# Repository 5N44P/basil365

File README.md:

# Basil365 (*ARCHIVED - ON HOLD*)
I want fresh basil all year round, but outdoors here it doesn't grow. Let's fix this, and make it IoT.

Buying a growlamp on the internet would be quite easy and cheap, but wouldn't make for a great DIY IoT project, so who cares, i'm going to roll my own IoT growlamp. And i want it to be the best and most efficient growlamp ever made. Since we are there, why not adding a load of sensors and connect it to a telegram bot to harass you? Seems great, let's do it.  

Led board without drivers

Test board (arduino shield) to assess the performance of various drivers and components 

## Initial research

Starting from the lamp, we want it led based. If you've ever seen a led growlamp before, you know that they are made of blue and red LEDs. But maybe we can do better. 

reference:  
https://www.growing-basil.org/artificial-lighting-for-growing-basil/ (secondary source)   
https://www.ncbi.nlm.nih.gov/pmc/articles/PMC5007804/  blue (450 nm), yellow/amber (600 nm), red (660 nm); 1:1:1; 150 μmol m−2 s−1    
https://www.sciencedirect.com/science/article/pii/S0304423815302892    
http://www.hortorumcultus.actapol.net/pub/13_2_3.pdf  

Design and fabrication of adjustable red-green-blue LED light arrays for plant research
https://www.ncbi.nlm.nih.gov/pmc/articles/PMC1198233/

umol/m2s to W/m2 equivalency
https://onlineconversion.vbulletin.net/forum/main-forums/convert-and-calculate/82240-%C2%B5mol-photons-m-2-s-1-to-led-watts

https://www.valoya.com/

Potential led:
Osram oslon ssl80

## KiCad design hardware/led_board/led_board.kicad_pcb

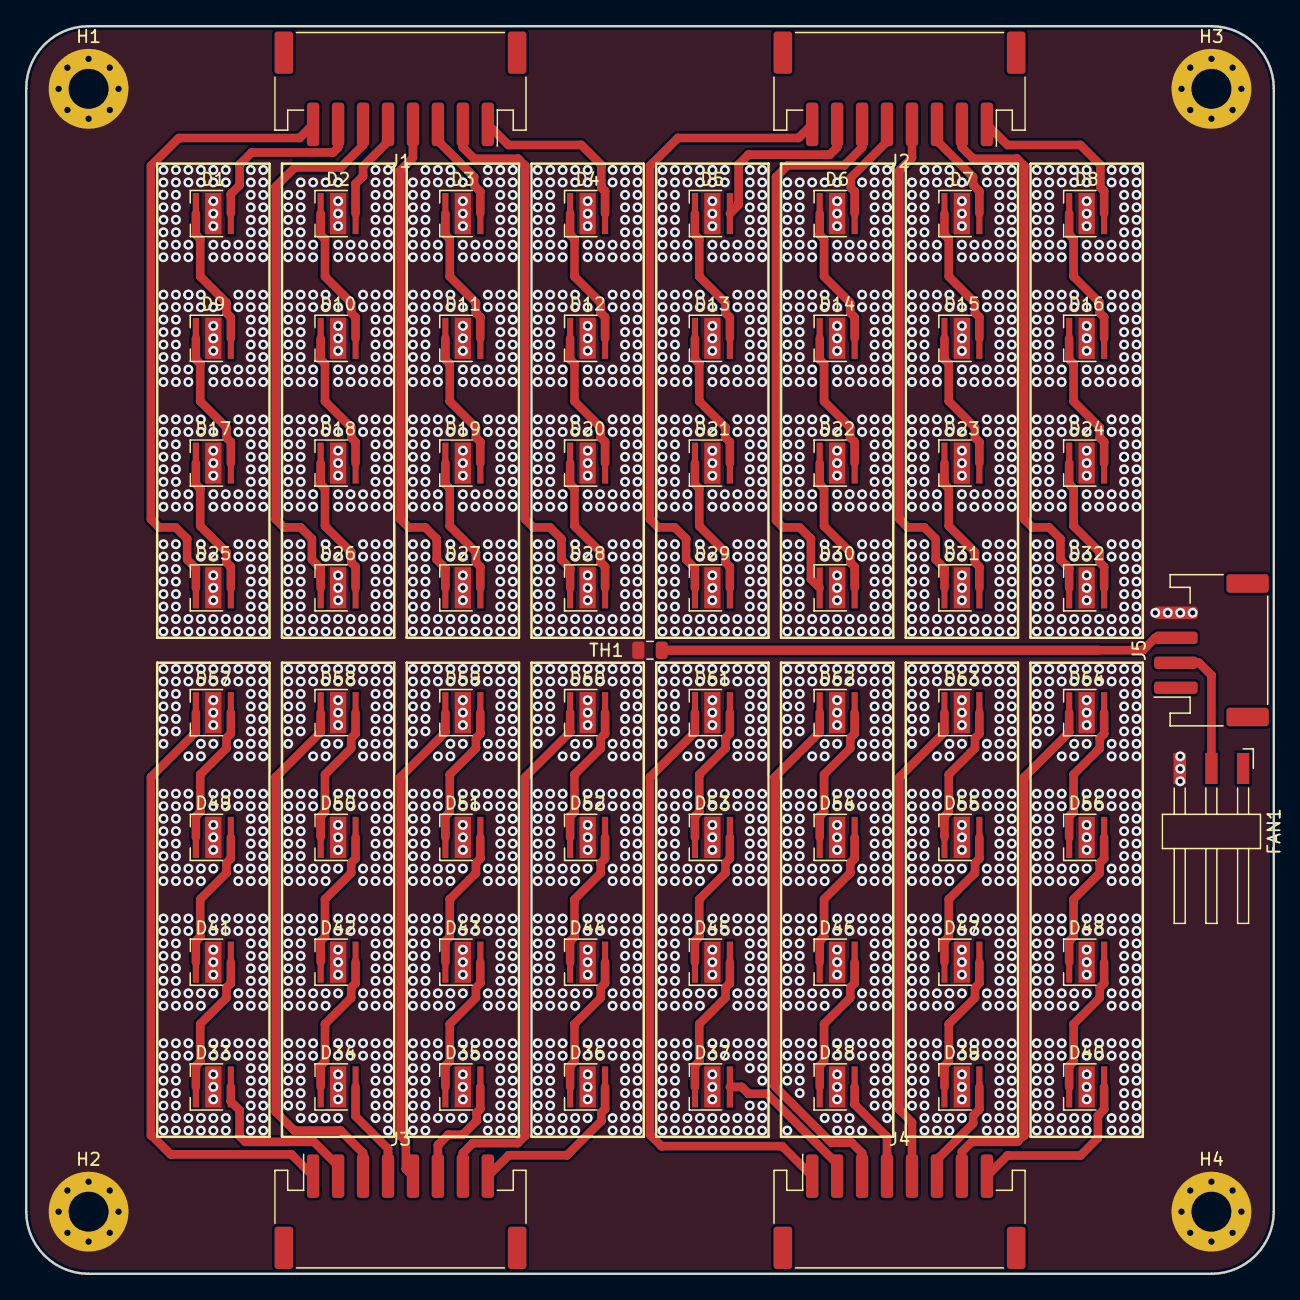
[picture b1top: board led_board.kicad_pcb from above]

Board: 2 copper layers, 100.0 x 100.0 mm, 75 parts (0 on the bottom side), 83 nets.

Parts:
D1, D2, D3, D4, D5, D6, D7, D8, D9, D10, D11, D12, D13, D14, D15, D16, D17, D18, D19, D20, D21, D22, D23, D24, D25, D26, D27, D28, D29, D30, D31, D32, D33, D34, D35, D36, D37, D38, D39, D40, D41, D42, D43, D44, D45, D46, D47, D48, D49, D50, D51, D52, D53, D54, D55, D56, D57, D58, D59, D60, D61, D62, D63, D64: LED_PAD; LED_Cree-XHP35
FAN1: Conn_01x03; Harwin_M20-89003xx_1x03_P2.54mm_Horizontal
H1, H2, H3, H4: MountingHole_Pad; MountingHole_3.2mm_M3_Pad_Via
J1, J2, J3, J4: NXW-08SMDK; JST_PH_S8B-PH-SM4-TB_1x08-1MP_P2.00mm_Horizontal
J5: Conn_01x04; JST_PH_S4B-PH-SM4-TB_1x04-1MP_P2.00mm_Horizontal
TH1: Thermistor_NTC; R_0805_2012Metric

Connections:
DRV1_A: D1.2, J1.7
DRV1_K: D25.1, J1.8
DRV2_A: D2.2, J1.5
DRV2_K: D26.1, J1.6
DRV3_A: D3.2, J1.3
DRV3_K: D27.1, J1.4
DRV4_A: D4.2, J1.1
DRV4_K: D28.1, J1.2
DRV5_A: D5.2, J2.7
DRV5_K: D29.1, J2.8
DRV6_A: D6.2, J2.5
DRV6_K: D30.1, J2.6
DRV7_A: D7.2, J2.3
DRV7_K: D31.1, J2.4
DRV8_A: D8.2, J2.1
DRV8_K: D32.1, J2.2
DRV9_A: D33.2, J3.2
DRV9_K: D57.1, J3.1
DRV10_A: D34.2, J3.4
DRV10_K: D58.1, J3.3
DRV11_A: D35.2, J3.6
DRV11_K: D59.1, J3.5
DRV12_A: D36.2, J3.8
DRV12_K: D60.1, J3.7
DRV13_A: D37.2, J4.2
DRV13_K: D61.1, J4.1
DRV14_A: D38.2, J4.4
DRV14_K: D62.1, J4.3
DRV15_A: D39.2, J4.6
DRV15_K: D63.1, J4.5
DRV16_A: D40.2, J4.8
DRV16_K: D64.1, J4.7
FAN_PWM: FAN1.2, J5.2
GND: D1.3, D2.3, D3.3, D4.3, D5.3, D6.3, D7.3, D8.3, D9.3, D10.3, D11.3, D12.3, D13.3, D14.3, D15.3, D16.3, D17.3, D18.3, D19.3, D20.3, D21.3, D22.3, D23.3, D24.3, D25.3, D26.3, D27.3, D28.3, D29.3, D30.3, D31.3, D32.3, D33.3, D34.3, D35.3, D36.3, D37.3, D38.3, D39.3, D40.3, D41.3, D42.3, D43.3, D44.3, D45.3, D46.3, D47.3, D48.3, D49.3, D50.3, D51.3, D52.3, D53.3, D54.3, D55.3, D56.3, D57.3, D58.3, D59.3, D60.3, D61.3, D62.3, D63.3, D64.3, FAN1.3, H1.1, H2.1, H3.1, H4.1, J5.4, TH1.1
unnamed: D1.1, D9.2
unnamed: D10.1, D18.2
unnamed: D2.1, D10.2
unnamed: D11.1, D19.2
unnamed: D3.1, D11.2
unnamed: D12.1, D20.2
unnamed: D4.1, D12.2
unnamed: D13.1, D21.2
unnamed: D5.1, D13.2
unnamed: D14.1, D22.2
unnamed: D6.1, D14.2
unnamed: D15.1, D23.2
unnamed: D7.1, D15.2
unnamed: D16.1, D24.2
unnamed: D8.1, D16.2
unnamed: D17.1, D25.2
unnamed: D9.1, D17.2
unnamed: D18.1, D26.2
unnamed: D19.1, D27.2
unnamed: D20.1, D28.2
unnamed: D21.1, D29.2
unnamed: D22.1, D30.2
unnamed: D23.1, D31.2
unnamed: D24.1, D32.2
unnamed: D33.1, D41.2
unnamed: D34.1, D42.2
unnamed: D35.1, D43.2
unnamed: D36.1, D44.2
unnamed: D37.1, D45.2
unnamed: D38.1, D46.2
unnamed: D39.1, D47.2
unnamed: D40.1, D48.2
unnamed: D41.1, D49.2
unnamed: D42.1, D50.2
unnamed: D43.1, D51.2
unnamed: D44.1, D52.2
unnamed: D45.1, D53.2
unnamed: D46.1, D54.2
unnamed: D47.1, D55.2
unnamed: D48.1, D56.2
unnamed: D49.1, D57.2
unnamed: D50.1, D58.2
unnamed: D51.1, D59.2
unnamed: D52.1, D60.2
unnamed: D53.1, D61.2
unnamed: D54.1, D62.2
unnamed: D55.1, D63.2
unnamed: D56.1, D64.2
TEMP_SENSE: J5.3, TH1.2

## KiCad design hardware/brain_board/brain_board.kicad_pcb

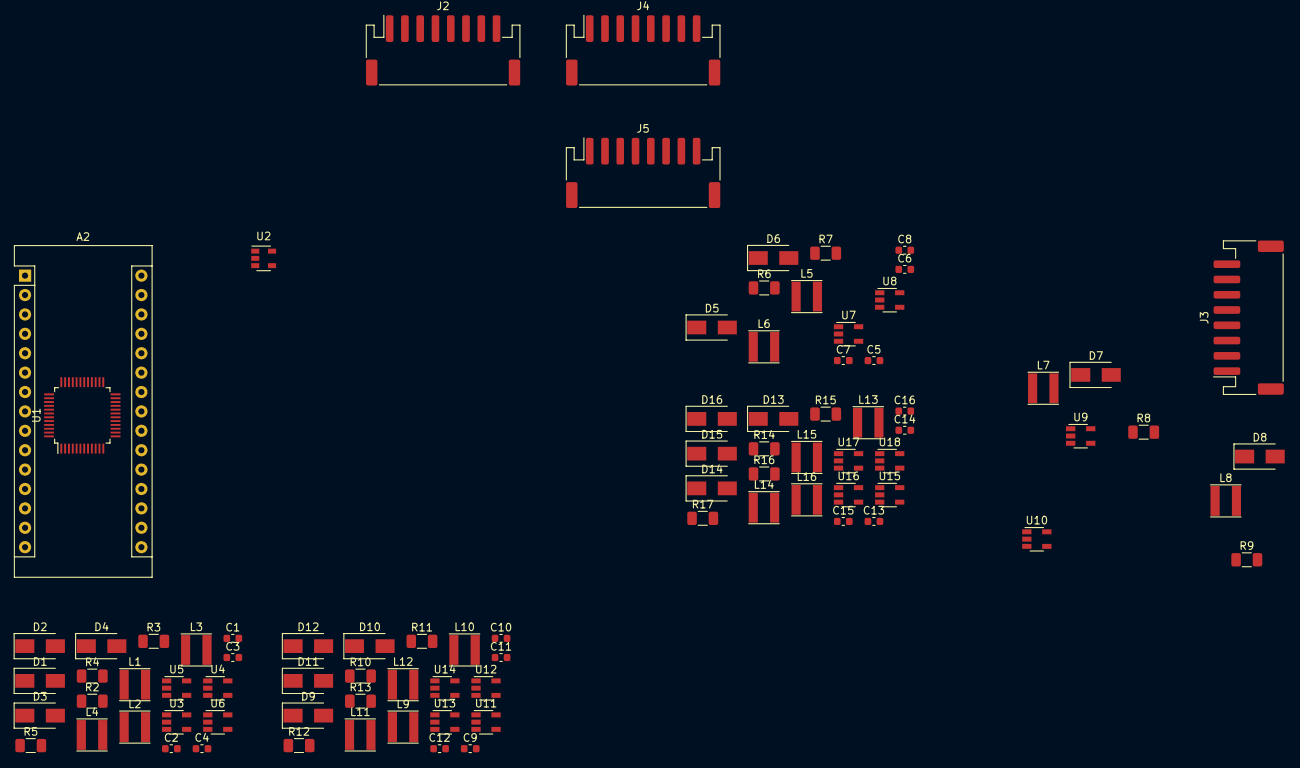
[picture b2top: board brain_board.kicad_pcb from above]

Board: 2 copper layers, 87 parts (0 on the bottom side), 89 nets, no tracks yet.

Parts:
A2: Arduino_Nano_Every; Arduino_Nano
C1, C2, C3, C4, C5, C6, C7, C8, C9, C10, C11, C12, C13, C14, C15, C16: 10u X7R; C_0603_1608Metric
D1, D2, D3, D4, D5, D6, D7, D8, D9, D10, D11, D12, D13, D14, D15, D16: SS14-DC; D_SMA
J2, J3, J4, J5: Conn_01x08_MountingPin; JST_PH_S8B-PH-SM4-TB_1x08-1MP_P2.00mm_Horizontal
L1, L2, L3, L4, L5, L6, L7, L8, L9, L10, L11, L12, L13, L14, L15, L16: 68u; L_Taiyo-Yuden_NR-40xx
R2, R3, R4, R5, R6, R7, R8, R9, R10, R11, R12, R13, R14, R15, R16, R17: 0.3R; R_1206_3216Metric
U1: ATmega4809-A; TQFP-48_7x7mm_P0.5mm
U2: INA168; SOT-23-5
U3, U4, U5, U6, U7, U8, U9, U10, U11, U12, U13, U14, U15, U16, U17, U18: AL8860WT-7; TSOT-23-5

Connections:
A0: A2.19, U1.23
A1: A2.20, U1.22
A2: A2.21, U1.21
A3: A2.22, U1.20
A4: A2.23, U1.46
A5: A2.24, U1.47
A6: A2.25, U1.24
A7: A2.26, U1.25
D2: A2.5, U1.44
D3: A2.6, U1.39
D4: A2.7, U1.18
D5: A2.8, U1.6
D6: A2.9, U1.38
D7: A2.10, U1.45
D8: A2.11, U1.33
D9: A2.12, U1.4
D10: A2.13, U1.5
GND: C1.2, C2.2, C3.2, C4.2, C5.2, C6.2, C7.2, C8.2, C9.2, C10.2, C11.2, C12.2, C13.2, C14.2, C15.2, C16.2, U3.2, U4.2, U5.2, U6.2, U7.2, U8.2, U9.2, U10.2, U11.2, U12.2, U13.2, U14.2, U15.2, U16.2, U17.2, U18.2
MASTER_RX: A2.1, U1.16
MASTER_TX: A2.2, U1.17
MISO: A2.15, U1.31
MOSI: A2.14, U1.30
unnamed: C1.1, D1.1, R2.1
unnamed: C2.1, D2.1, R3.1
unnamed: C3.1, D3.1, R4.1
unnamed: C4.1, D4.1, R5.1
unnamed: C5.1, D5.1, R6.1
unnamed: C6.1, D6.1, R7.1
unnamed: C7.1, D7.1, R8.1
unnamed: C8.1, D8.1, R9.1
unnamed: C9.1, D9.1, R10.1
unnamed: C10.1, D10.1, R11.1
unnamed: C11.1, D11.1, R12.1
unnamed: C12.1, D12.1, R13.1
unnamed: C13.1, D13.1, R14.1
unnamed: C14.1, D14.1, R15.1
unnamed: C15.1, D15.1, R16.1
unnamed: C16.1, D16.1, R17.1
unnamed: D1.2, L1.1, U3.1
unnamed: D2.2, L2.1, U4.1
unnamed: D3.2, L3.1, U5.1
unnamed: D4.2, L4.1, U6.1
unnamed: D5.2, L5.1, U7.1
unnamed: D6.2, L6.1, U8.1
unnamed: D7.2, L7.1, U9.1
unnamed: D8.2, L8.1, U10.1
unnamed: D9.2, L9.1, U11.1
unnamed: D10.2, L10.1, U12.1
unnamed: D11.2, L11.1, U13.1
unnamed: D12.2, L12.1, U14.1
unnamed: D13.2, L13.1, U15.1
unnamed: D14.2, L14.1, U16.1
unnamed: D15.2, L15.1, U17.1
unnamed: D16.2, L16.1, U18.1
unnamed: J2.1, R5.2, U6.4
unnamed: J2.2, L4.2
unnamed: J2.3, R4.2, U5.4
unnamed: J2.4, L3.2
unnamed: J2.5, R3.2, U4.4
unnamed: J2.6, L2.2
unnamed: J2.7, R2.2, U3.4
unnamed: J2.8, L1.2
unnamed: J3.1, R9.2, U10.4
unnamed: J3.2, L8.2
unnamed: J3.3, R8.2, U9.4
unnamed: J3.4, L7.2
unnamed: J3.5, R7.2, U8.4
unnamed: J3.6, L6.2
unnamed: J3.7, R6.2, U7.4
unnamed: J3.8, L5.2
unnamed: J4.1, R13.2, U14.4
unnamed: J4.2, L12.2
unnamed: J4.3, R12.2, U13.4
unnamed: J4.4, L11.2
unnamed: J4.5, R11.2, U12.4
unnamed: J4.6, L10.2
unnamed: J4.7, R10.2, U11.4
unnamed: J4.8, L9.2
unnamed: J5.1, R17.2, U18.4
unnamed: J5.2, L16.2
unnamed: J5.3, R16.2, U17.4
unnamed: J5.4, L15.2
unnamed: J5.5, R15.2, U16.4
unnamed: J5.6, L14.2
unnamed: J5.7, R14.2, U15.4
unnamed: J5.8, L13.2
unnamed: U1.14, U1.42
unnamed: U1.15, U1.29, U1.43
SCK: A2.16, U1.32

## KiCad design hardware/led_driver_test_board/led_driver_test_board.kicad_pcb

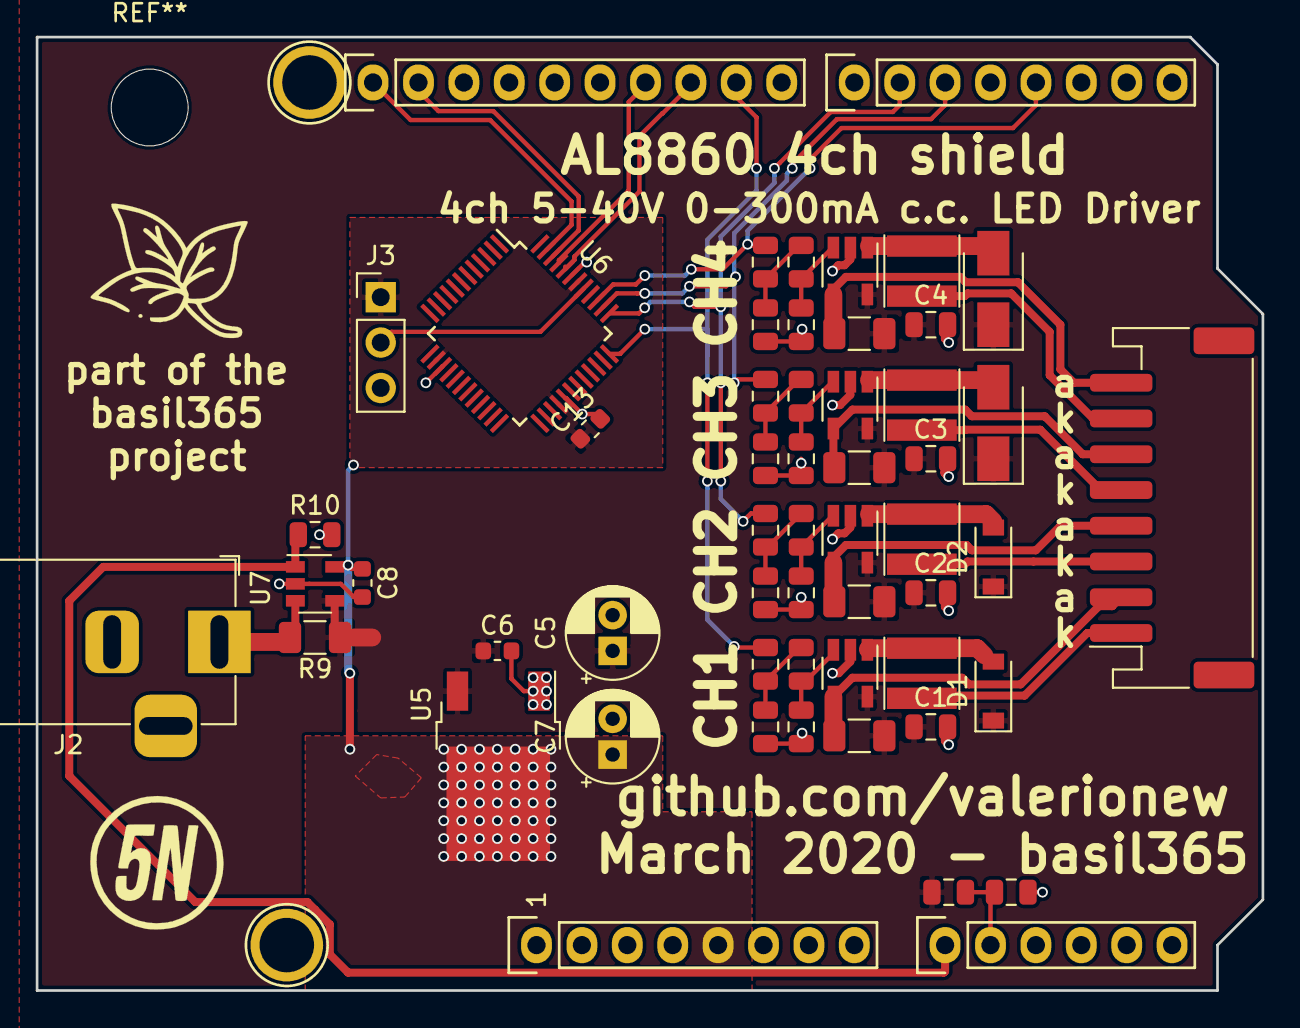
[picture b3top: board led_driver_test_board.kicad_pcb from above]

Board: 2 copper layers, 68.6 x 53.3 mm, 57 parts (0 on the bottom side), 35 nets.

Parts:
C1, C2, C3, C4, C9, C10, C11, C12: 10u X7R; C_0805_2012Metric
C5, C7: 22u; CP_Radial_D5.0mm_P2.00mm
C6, C8, C13: 100n; C_0603_1608Metric
D1, D2: STPS0540Z; D_SOD-123
D3, D4: SS14-DC; D_SMA
J1: Conn_01x08_MountingPin; JST_PH_S8B-PH-SM4-TB_1x08-1MP_P2.00mm_Horizontal
J2: Barrel_Jack_Switch; BarrelJack_Horizontal
J3: Conn_01x03; PinHeader_1x03_P2.54mm_Vertical
L1, L2, L3, L4: 68u; L_Taiyo-Yuden_NR-40xx
P1: Digital; Socket_Strip_Arduino_1x10
P2: Power; Socket_Strip_Arduino_1x08
P3: Digital; Socket_Strip_Arduino_1x08
P4: Analog; Socket_Strip_Arduino_1x06
P5, P7: CONN_01X01; Arduino_1pin
R1, R2, R3, R4: 0.3R; R_1206_3216Metric
R5, R6, R7, R8, R11, R12, R13, R14, R15, R16, R17, R18, R20: 10k; R_0805_2012Metric
R9: 0R1; R_1206_3216Metric
R10: R; R_0805_2012Metric
R19: 33k; R_0805_2012Metric
U1, U2, U3, U4: AL8860WT-7; TSOT-23-5
U5: AZ1117-5.0; TO-252-2
U6: ATmega4809-A; TQFP-48_7x7mm_P0.5mm
U7: INA138; SOT-23-5

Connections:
+5V: C7.1, C8.1, C13.1, J3.1, P2.5, U5.2, U6.14, U6.28, U6.42, U7.5
/3(**): P3.5, R17.2, U6.39
/5(**): P3.3, R15.2, U6.38
/6(**): P3.2, R13.2, U6.37
/9(**): P1.9, R11.2, U6.36
/10(**/SS): P1.8, U6.44
/11(**/MOSI): P1.7, U6.45
/A0: P4.1, R10.1, U7.1
/A1: P4.2, R19.2, R20.1
/A4(SDA): P1.2, P4.5, U6.46
/A5(SCL): P1.1, P4.6, U6.47
/CH1: C9.1, R5.1, U1.3
/CH2: C10.1, R6.1, U2.3
/CH3: C11.1, R7.1, U3.3
/CH4: C12.1, R8.1, U4.3
GND: C1.2, C2.2, C3.2, C4.2, C5.2, C6.2, C7.2, C8.2, C9.2, C10.2, C11.2, C12.2, C13.2, J2.2, J2.3, J3.3, P1.4, P2.6, P2.7, R10.2, R12.2, R14.2, R16.2, R18.2, R20.2, U1.2, U2.2, U3.2, U4.2, U5.1, U6.15, U6.29, U6.43, U7.2
unnamed: D1.2, L1.1, U1.1
unnamed: D2.2, L2.1, U2.1
unnamed: D3.2, L3.1, U3.1
unnamed: D4.2, L4.1, U4.1
unnamed: J1.1, L1.2
unnamed: J1.2, R1.2, U1.4
unnamed: J1.3, L2.2
unnamed: J1.4, R2.2, U2.4
unnamed: J1.5, L3.2
unnamed: J1.6, R3.2, U3.4
unnamed: J1.7, L4.2
unnamed: J1.8, R4.2, U4.4
unnamed: J2.1, R9.1, U7.3
unnamed: J3.2, U6.41
unnamed: R5.2, R11.1, R12.1
unnamed: R6.2, R13.1, R14.1
unnamed: R7.2, R15.1, R16.1
unnamed: R8.2, R17.1, R18.1
Vdrive: C1.1, C2.1, C3.1, C4.1, C5.1, C6.1, D1.1, D2.1, D3.1, D4.1, R1.1, R2.1, R3.1, R4.1, R9.2, R19.1, U1.5, U2.5, U3.5, U4.5, U5.3, U7.4

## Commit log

2019-10-01 first commit on initial research
2019-10-01 Fixing my broxxen inglish
2019-10-20 Added potential reference source
2019-10-20 Potential lef
2019-10-21 Typo in readme
2021-09-21 Added board design files and images
2021-09-21 fixed readme
2021-09-21 Archiving
